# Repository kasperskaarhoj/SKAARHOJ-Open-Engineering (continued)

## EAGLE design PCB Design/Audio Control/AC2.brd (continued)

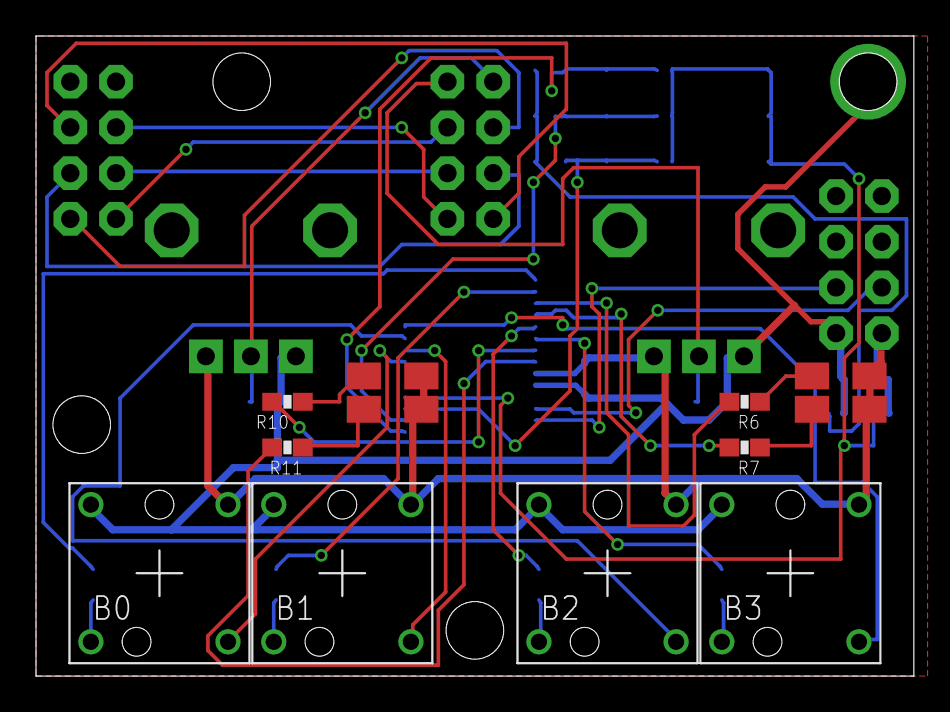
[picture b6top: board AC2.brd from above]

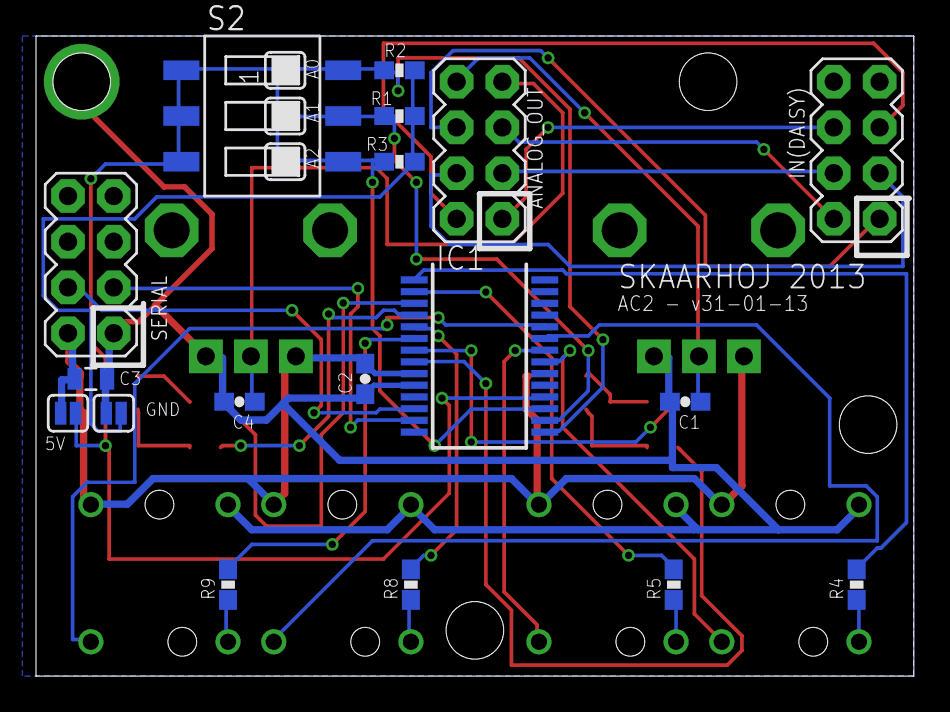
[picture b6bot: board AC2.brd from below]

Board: 2 copper layers, 48.8 x 35.6 mm, 33 parts (21 on the bottom side), 37 nets.
